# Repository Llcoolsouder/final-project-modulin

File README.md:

# Modulin
A _modulin_ is an electronic, violin-esque, musical instrument. The original modulin was created by Martin Molin of Wintergatan.
Footage of the orignal instrument can be found [here](https://www.youtube.com/watch?v=MUdWeBYe3GY). 

Created by:
Lonnie L. Souder II

final-project-modulin created by GitHub Classroom

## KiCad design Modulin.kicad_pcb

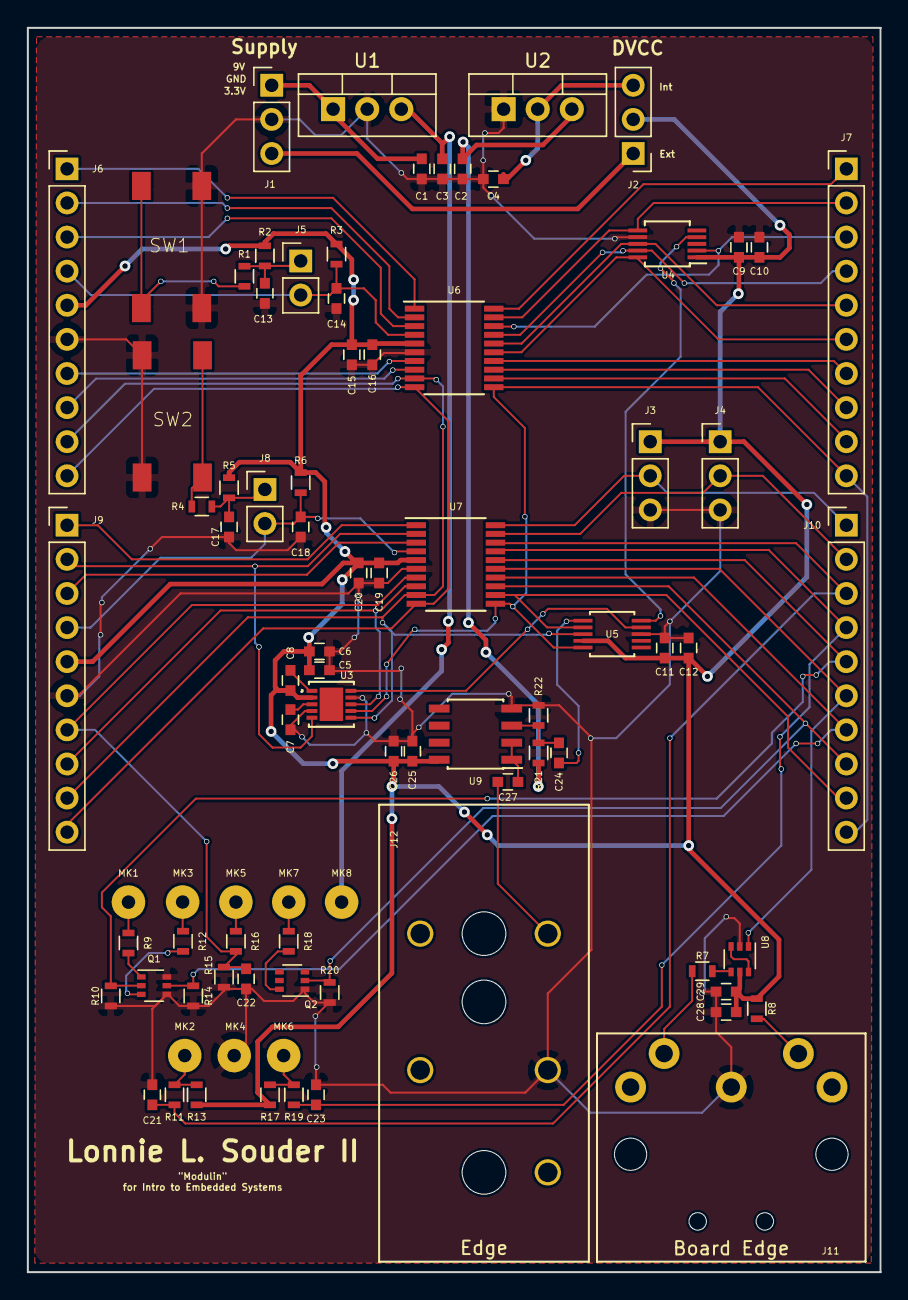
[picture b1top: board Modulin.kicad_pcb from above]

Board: 2 copper layers, 63.5 x 92.7 mm, 84 parts (0 on the bottom side), 64 nets.

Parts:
C1, C2, C16, C20: 100n; C_0603
C3, C4, C6: 10u; C_0603
C5, C7, C9: 0.1u; C_0603
C8, C12, C13, C17, C21, C22, C23, C26, C29: 10n; C_0603
C10, C11, C15, C19, C24, C25, C27, C28: 1u; C_0603
C14, C18: 1n; C_0603
J1, J2: Conn_01x03_Male; Pin_Header_Straight_1x03_Pitch2.54mm
J3, J4: Conn_01x03_Female; Pin_Header_Straight_1x03_Pitch2.54mm
J5, J8: Conn_01x02_Male; Pin_Header_Straight_1x02_Pitch2.54mm
J6, J7, J9, J10: Conn_01x10_Male; Pin_Header_Straight_1x10_Pitch2.54mm
J11: DIN-5_180degree; SDS-50J
J12: Audio-Jack-2; SN37A14B
MK1, MK2, MK3, MK4, MK5, MK6, MK7, MK8: Mounting_Hole_PAD; SolderWirePad_single_1mmDrill
Q1, Q2: DMN63D8LDW-7; SOT-363_SC-70-6
R1, R2, R4, R5, R11, R13, R15, R16, R17, R19: 10k; R_0603
R3, R6: 47; R_0603
R7, R8: 220; R_0603
R9: 320; R_0603
R10, R14, R20: 1M; R_0603
R12, R18: 170; R_0603
R21, R22: 500k; R_0603
SW1, SW2: SW_Push; FSM2JSMAATR
U1: LM7805CT; TO-220-3_Vertical
U2: LD1117V33; TO-220-3_Vertical
U3: AD9837BCPZ-RL7
U4: MCP48FVB21-E/UN; MSOP-10_3x3mm_Pitch0.5mm
U5: MAX4587EUB+; MAX4587EUB&plus_
U6, U7: MSP430FR2311IPW20R; TSSOP-20_4.4x6.5mm_Pitch0.65mm
U8: NL27WZ04DFT1G; SOT-363_SC-70-6
U9: TSH22IDT; SOIC-8_3.9x4.9mm_Pitch1.27mm

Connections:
+3V3: J1.3, J2.1
+5V: C3.1, MK8.1, U1.3
+9V: C1.1, C2.1, J1.1, R21.1, U1.1, U2.3
/AudioOut/AudioOut: C24.2, U5.1
/FR2311_setup1/P1.0: J6.2, U6.2
/FR2311_setup1/P1.1: J6.1, U6.1
/FR2311_setup1/P1.2: J7.1, U6.20
/FR2311_setup1/P1.3: J7.2, U4.6, U6.19
/FR2311_setup1/P1.4: J7.3, U4.2, U6.18
/FR2311_setup1/P1.5: J7.4, U4.9, U6.17
/FR2311_setup1/P1.6: J7.5, U4.8, U6.16
/FR2311_setup1/P1.7: J7.6, U4.10, U6.15
/FR2311_setup1/P2.0: J7.7, U6.14
/FR2311_setup1/P2.1: J7.8, U6.13
/FR2311_setup1/P2.2: J7.9, U6.12
/FR2311_setup1/P2.3: J7.10, J10.10, U3.7, U5.5, U6.11, U7.11
/FR2311_setup1/P2.4: J6.9, J9.9, U3.6, U5.3, U6.9, U7.9
/FR2311_setup1/P2.5: J6.10, J9.10, U6.10, U7.10
/FR2311_setup1/P2.6: J6.8, U6.8
/FR2311_setup1/P2.7: J6.7, U6.7
/FR2311_setup1/TEST: J6.3, U6.3
/FR2311_setup1/~RST: C14.2, J5.2, J6.4, R3.1, U6.4
/FR2311_setup2/P1.0: J9.2, U3.5, U7.2
/FR2311_setup2/P1.1: J9.1, U7.1
/FR2311_setup2/P1.2: J3.2, J10.1, U7.20
/FR2311_setup2/P1.3: J4.2, J10.2, U7.19
/FR2311_setup2/P1.6: J10.5, Q1.2, R10.1, U7.16
/FR2311_setup2/P2.0: J10.7, Q1.5, R14.1, U7.14
/FR2311_setup2/P2.1: J10.8, Q2.2, R20.1, U7.13
/FR2311_setup2/P2.2: J10.9, U5.2, U7.12
/FR2311_setup2/P2.6: J9.8, U3.8, U7.8
/FR2311_setup2/TEST: J9.3, U7.3
/FR2311_setup2/~RST: C18.2, J8.2, J9.4, R6.1, U7.4
/MIDI_out/DataOut: J10.6, U7.15, U8.1
/RGB_Encoder/A: C21.1, J10.3, R11.2, U7.18
/RGB_Encoder/B: C23.1, J10.4, R19.1, U7.17
/RGB_Encoder/Btn: C22.1, J9.7, R15.1, R16.2, U7.7
DVCC: C5.1, C6.1, C8.1, C9.1, C10.1, C11.1, C12.1, C15.1, C16.1, C19.1, C20.1, C25.2, C26.1, C28.1, C29.1, J2.2, J3.1, J4.1, J6.5, J9.5, R2.1, R3.2, R5.1, R6.2, R8.1, R13.1, R17.2, U3.2, U4.1, U5.4, U6.5, U7.5, U8.5, U9.8
GNDD: C1.2, C2.2, C3.2, C4.2, C5.2, C6.2, C7.2, C9.2, C10.2, C11.2, C12.2, C13.2, C14.1, C15.2, C16.2, C17.2, C18.1, C19.2, C20.2, C21.2, C22.2, C23.2, C25.1, C26.2, C28.2, C29.2, J1.2, J3.3, J4.3, J6.6, J9.6, J11.2, J12.2, MK4.1, Q1.4, Q1.6, Q2.1, R10.2, R14.2, R15.2, R20.2, R22.2, SW1.1, SW2.1, U1.2, U2.1, U3.4, U3.9, U4.7, U5.8, U6.6, U7.6, U8.2, U9.4
unnamed: C4.1, J2.3, U2.2
unnamed: C7.1, U3.3
unnamed: C8.2, U3.1
unnamed: C13.1, J5.1, R1.1, R2.2
unnamed: C17.1, J8.1, R4.1, R5.2
unnamed: C24.1, R21.2, R22.1, U9.3
unnamed: C27.1, J12.1
unnamed: C27.2, U9.1, U9.2
unnamed: J11.4, R8.2
unnamed: J11.5, R7.1
unnamed: MK1.1, R9.1
unnamed: MK2.1, R11.1, R13.2
unnamed: MK3.1, R12.1
unnamed: MK5.1, R16.1
unnamed: MK6.1, R17.1, R19.2
unnamed: MK7.1, R18.1
unnamed: Q1.1, R9.2
unnamed: Q1.3, R12.2
unnamed: Q2.6, R18.2
unnamed: R1.2, SW1.2
unnamed: R4.2, SW2.2
unnamed: R7.2, U8.4
unnamed: U3.10, U5.9
unnamed: U4.4, U5.10
unnamed: U8.3, U8.6

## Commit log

2017-11-16 PCB schematic started
2017-11-17 Schematic for JUST making sound.
2017-11-21 Moving towards distributed architecture and heirarchical schematic
2017-11-21 Added sheet for MIDI out
2017-11-21 Created README
2017-11-21 fixed README typo
2017-11-21 update to MIDI out sheet
2017-11-22 Added circuit for encoder
2017-11-22 Finished Rev1 schematic and assigned most footprints
2017-11-23 Associated all footprints except jacks
2017-11-23 Created all footprints. Started TimerLib
2017-11-26 Finished board Rev 1
2017-11-26 Halfway through layout. Started libraries.
2017-11-27 Created Gerbers
2017-12-04 Started libs for peripherals
2017-12-08 Tested basic functions of SPILib
2017-12-10 Fixed 3D models
2017-12-20 Started Modulin CCS project. Added multi-byte message for SPI
2017-12-20 Added function to set frequency of wave gen
2018-01-07 Created MIDI libraries and defined macros for common messages

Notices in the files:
parts and their libraries:
Copyright 2016 Accelerated Designs. All rights reserved.
